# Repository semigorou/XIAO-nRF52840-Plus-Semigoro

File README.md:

# XIAO nRF52840 Plus - Semigorou

Rev Oでは、Plusの追加端子D11〜D19に対応するφ0.65 mm穴を左右9個ずつ設け、左右ともD0〜D19の接続点を用意しました。使用中の信号は既存回路へ接続し、未使用端子も取り出せます。D16は電池測定、D14/D15はNFC兼用です。接触・はんだ付け方法は未確定で、穴を設けただけではXIAOと自動接続しません。通常端子のパッド径は1.4 mm（穴径1.0 mm）、信号配線幅は基本0.15 mm・最小0.13 mm、信号間隔0.15 mmです。DRC違反0・未接続0を確認しました。

B面の左右に2行で印字しました。1行目は https://github.com/semigorou、2行目は XIAO nRF52840 Plus - Semigorou です。B面を正面から見て、左は上から下、右は下から上へ読める向きです。

> **Rev Oの取付構成は、左右ともXIAOをB面、電源スイッチ・RESETボタンをF面です。** 左XIAOの14端子と左スイッチ配置を反転して再配線し、出力Gerberの実装面と位置決め穴も検証しました。基板にはXIAO B・PWR F・RST FおよびF/Bを印字しています。

Y13 Rev O試作基板とXIAO用ZMK設定。Rev OでもGPIO信号の割当はRev Gから維持しています。左右各XIAO nRF52840 Plus、左エンコーダー、右PMW3610に対応する試作用ファームウェアです。ビルド成功と実機動作確認は別です。実機試験はこれからです。
またPCBについては、もともとnice!nano v2を搭載するPCBをベースに設計してます。nice!nano v2はBluetooth通信に対応していますが、日本の技適認証を取得していないため、日本国内での使用を想定し、技適認証に対応したXIAO nRF52840 Plusへ変更しました。

## Rev O 基板の発注データ

**[発注用Gerber ZIP](hardware/revO/Y13-XIAO-revO-order-gerbers.zip?raw=true)** · **[基板画像・発注／組立メモ](hardware/revO/README.md)**

2層・FR-4・板厚1.6 mm。XIAOの部品面をキャリアへ向けるRev Oです。旧Rev G以前のGerberは使用しないでください。取付高さと支持部材は実物で調整する前提の少量試作用で、ケース適合・電池充電・実機動作は未検証です。

左4×6＋5＝29キー、右4×6＋3＝27キー＋トラックボールに対応します。UF2名のrevGは既存ファームウェアの名前で、旧基板の取付方向を示すものではありません。

## 構成

- **右が親機（central）**。PCへのUSB／Bluetooth接続は右側を使います。左は子機。
- 左右各5行×6列。既存キーマップの配置・4レイヤー・56キーの割当を継承。60キー分のGPIOがあっても、空いている4位置は現キーマップに登録していません。
- 左エンコーダー：D6/P1.11、D8/P1.13、GND。
- 右PMW3610：SCLK D8/P1.13、SDIO D19/P1.07、NCS D13/P1.01、MOTION D6/P1.11。SPIのMOSI/MISOは同じSDIO線です。
- 左J7の予備D13/P1.01、D17/P1.03、D18/P1.05は予約のみ。キー等へ割り当てず、ファームウェアから駆動しません。
- 電池電圧はXIAO標準のP0.31とP0.14制御の分圧回路で取得。
- 充電電流選択P0.13は起動時に無プル入力とし、公称約50 mAを選びます。**D13/P1.01とは別ピン**です。100 mAモードは実装していません。
- RF送信出力を独自に上げる設定は移植していません。ソフトウェアだけで技適や組立後の無線適合を保証するものではありません。

ZMK v0.3の固定コミットと、元のDoctorWangWang PMW3610ドライバーの固定コミットを使用します。v0.3でのボード名は`seeeduino_xiao_ble`です。Plusの追加端子はGPIO番号で指定します。外付けQSPIフラッシュは使わず、設定はnRF内部フラッシュへ保存します。

## ダウンロードと書き込み

1. このリポジトリの **Actions → Build XIAO Plus Rev G firmware** を開き、成功した実行の`firmware`をダウンロード・展開します。
2. 初回またはペアリング不整合時は、左右ともRESETを素早く2回押してUSBドライブを表示し、`charybdis-xiao-plus-settings-reset.uf2`を各XIAOへコピーします。保存済みペアリング等が消えます。
3. 再度ブートローダーへ入り、左には`charybdis-xiao-plus-revG-left.uf2`、右には`charybdis-xiao-plus-revG-right-central.uf2`をコピーします。
4. 両側を起動し、右をUSBでPCへ接続してキーを確認します。その後、PCからBluetoothの`Charybdis XIAO+`へ接続します。

PCB上のRESETボタンを使うにはキャリアRESET端子からXIAO TP2への追加線が必要です。電源スイッチは電池＋だけを切ります。USB接続中の完全な電源OFFではありません。

## 電池と通電前確認

3.7 V・満充電4.2 Vの単セル電池を左右に1個ずつ独立接続する構成です。**電池の許容充電電流・保護回路は未確認**で、キャリアに逆接保護はありません。電池の極性、電源―GND短絡、追加線の導通を確認し、最初は電池を外してUSBで確認してください。

内蔵充電ICの約10時間タイマーに対し、50 mAでは400 mAhも充電状態によって時間切れの可能性があり、1100 mAhを深い放電から1回で満充電する用途には適合未確認です。このファームウェアはタイマー制限を解決しません。電池の仕様確認と実測が必要です。充電には電源SWをONにします。

USB位置の公差、ピン・スペーサーの固定と絶縁、スイッチの実物適合、電池固定、ケース収納は別途確認が必要です。元のnice!nano用UF2は書き込まないでください。

## 配線・変更

`docs/wiring.csv`がRev OのXIAO―キャリア対応、`docs/trackball.csv`が右の横一列6端子です。D11〜D19はXIAOの追加端子位置に対応した穴で接続する構造に変更しました。従来の離れた追加配線用穴は置換しています。接触方法・ピン長・支持部材は別途選定が必要です。BAT+とRESETの追加接続も残ります。主端子14本だけでは全機能は接続されません。

行はD1/D2/D4/D5/D7、列はD3/D0/D9/D10/D11/D12。ダイオード方向は元設定の`row2col`を維持。ボール方向・感度は既存設定を継承し、実物で必要なら調整します。予備GPIOの用途を追加する場合は対応する設定も変更してください。

## 出典

- 元設定・キーマップ：https://github.com/Semigoro23/zmk-config-nicenanov2-GERBER-adapter_Y13 （b3e0c08964bd929275c06698c74caaf6f8720078）
- ZMK：https://github.com/zmkfirmware/zmk （edf5c0814fd3ea202e43aad2d68fd32e882a518c）
- PMW3610：https://github.com/DoctorWangWang/zmk-pmw3610-driver （1d9c2c68ca76012e1b1e5f6ef02fa5eadc4ca399）
- Seeed公式：https://wiki.seeedstudio.com/XIAO_BLE/
- 充電IC：https://www.ti.com/lit/ds/symlink/bq25100.pdf

既存ファイルの著作権・ライセンス表記を維持しています。上流ソースのライセンスは各リポジトリを参照してください。

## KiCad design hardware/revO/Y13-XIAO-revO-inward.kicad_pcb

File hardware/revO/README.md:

# XIAO nRF52840 Plus - Semigorou / Rev O

**[発注用Gerber ZIP](Y13-XIAO-revO-order-gerbers.zip?raw=true)**

FR-4・2層・板厚 **1.6 mm**。

Rev Oでは左右それぞれD11〜D19に対応するφ0.65 mmの追加穴を9個配置。D0〜D19の全接続点を用意。D16は電池電圧測定、D14/D15はNFC兼用。追加穴の接触・はんだ付け方法は未確定で、穴を増設するだけでXIAOと自動接続するものではない。BAT+とRESETの追加接続も残る。通常14端子のパッド径は1.4 mm、穴径1.0 mm。旧追加配線用の離れた端子穴は、新しい対応位置の穴へ置き換え。ネジ穴とUSB基準位置は維持。

B面の左右に1行目 https://github.com/semigorou、2行目 XIAO nRF52840 Plus - Semigorouを印字。B面を正面から見て、左は上から下、右は下から上へ読める向き。

|部品|左|右|
|---|---|---|
|XIAO nRF52840 Plus|B面|B面|
|RESETボタン|F面|F面|
|スライド電源|F面|F面|

XIAOの部品面はキャリアへ向ける。基板にはXIAO B、PWR F、RST F、F/Bを印字した。左の14端子をB面取付けに合わせて反転し、再配線している。

## F面

## B面から見た向き

## 配線・検証

- [取付と検証記録](verification-report.md)
- [ピン接続表](pin-connections.csv)
- [センサー配線表](trackball.csv)
- [DRC](drc.txt)は違反0・未配線0。
- [Gerber検証記録](verification.json)で基板とドリル位置を照合済み。電源の位置決め穴は左右2個ずつφ0.90 mm。

右下端子はF面からUSBを上に見てGND / MOTION / SCLK / SDIO / CS / VCC。

GPIO信号の割当は既存XIAO用ファームウェアと同じ。左右各5行6列で左29キー、右27キー＋トラックボールに対応する。

高さと支持部材は実物で調整する。修正版での実装・ケース適合・充電・無線動作は未検証。Rev J以前の取付構成・接続座標は旧版。

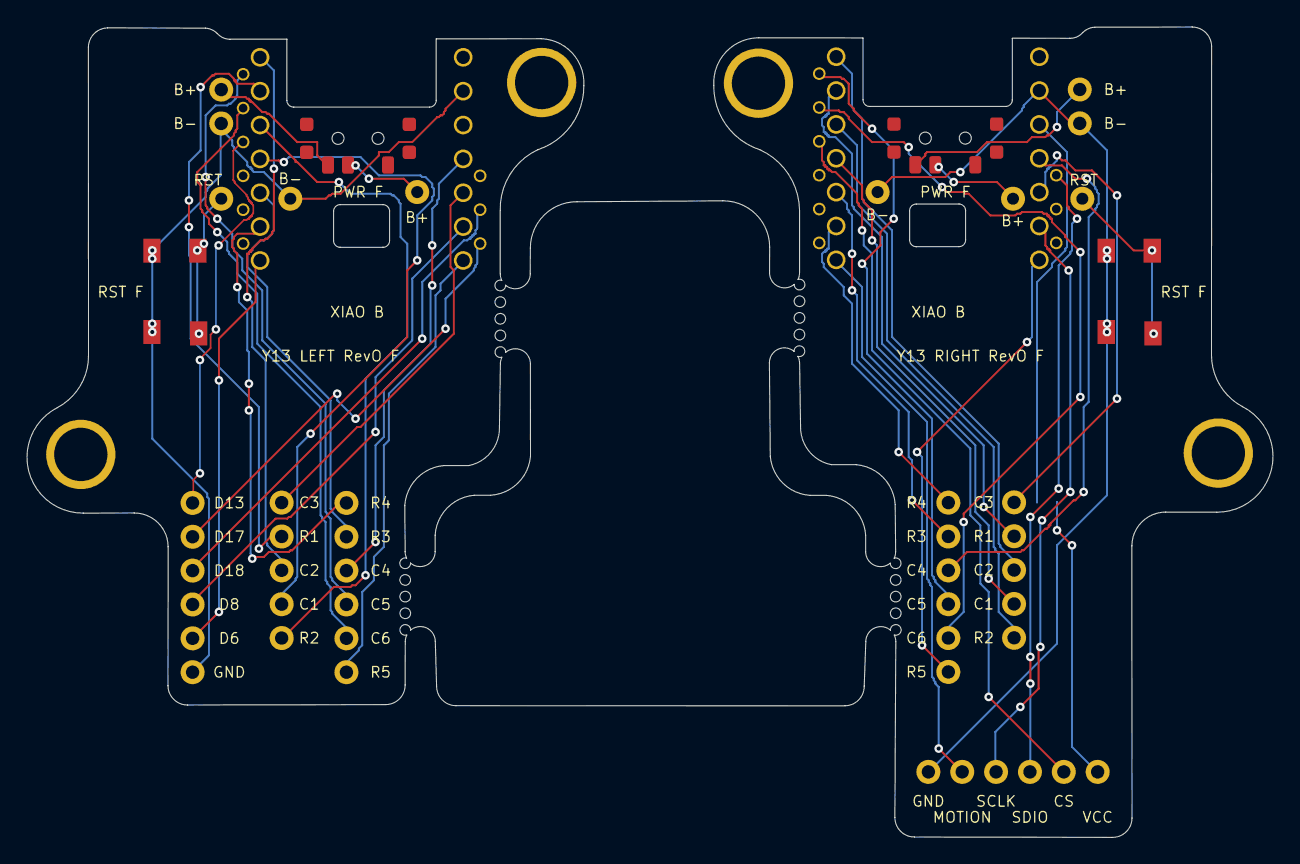
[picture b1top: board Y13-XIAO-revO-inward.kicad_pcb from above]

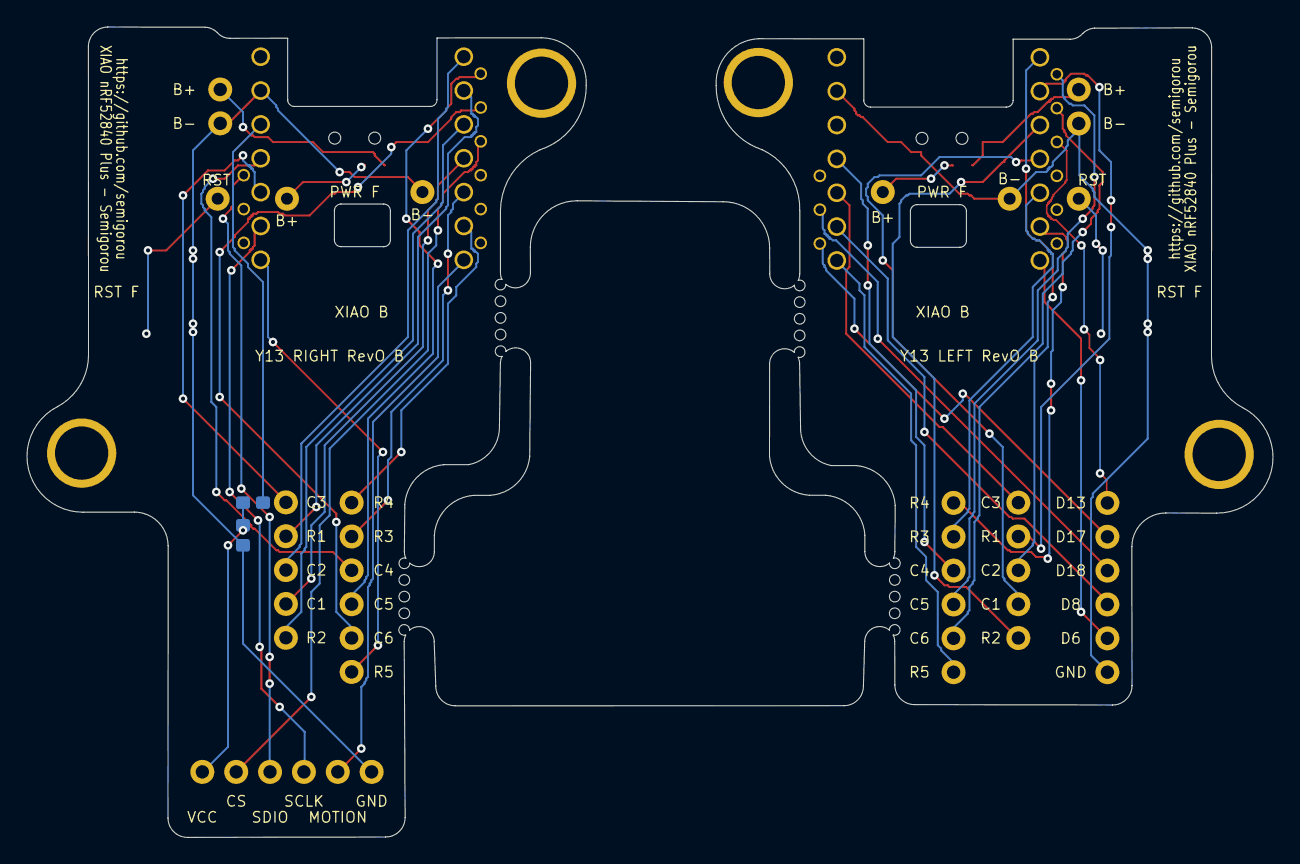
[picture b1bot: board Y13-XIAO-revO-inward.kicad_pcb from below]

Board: 2 copper layers, 93.5 x 60.8 mm, 28 parts (8 on the bottom side), 41 nets.

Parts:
C_SENSOR: 1uF 10V X7R 0603; C_SENSOR_DRAFT
J3: Original-position wire header; J3_DRAFT
J6: Original-position wire header; J6_DRAFT
J7: Original-position wire header; J7_DRAFT
J8: PMW3610 horizontal wire pads; J8_DRAFT
J9: Original-position wire header; J9_DRAFT
J10: Original-position wire header; J10_DRAFT
J11: Original-position wire header; J11_DRAFT
J12: Original-position wire header; J12_DRAFT
MB1, MB2, MB3, MB4, MB5, MB6, MB7, MB8, MB9, MB10, MB11, MB12: 0.8mm NPTH breakaway
R_SENSOR: 0R 0603; R_SENSOR_DRAFT
SW1, SW2: Original reset button
SW3: Reuse original slide switch; SW3_DRAFT
SW4: Reuse original slide switch; SW4_DRAFT
XIAO_L: XIAO Plus B SIDE; components toward carrier; XIAO_L_HEADER_DRAFT
XIAO_R: XIAO Plus B SIDE; components toward carrier; XIAO_R_HEADER_DRAFT

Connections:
3V3_R: R_SENSOR.1, XIAO_R.3V3
GND_L: J3.2, J7.6, SW1.2, XIAO_L.BAT-, XIAO_L.GND
GND_R: C_SENSOR.2, J6.2, J8.1, SW2.2, XIAO_R.BAT-, XIAO_R.GND
RESET_L: SW1.1, XIAO_L.RESET
RESET_R: SW2.1, XIAO_R.RESET
SENSOR_VDD_R: C_SENSOR.1, J8.6, R_SENSOR.2
SPARE_D13_L: J7.1, XIAO_L.D13
SPARE_D17_L: J7.2, XIAO_L.D17
SPARE_D18_L: J7.3, XIAO_L.D18
bat_l: SW3.2, XIAO_L.BAT+
bat_r: SW4.2, XIAO_R.BAT+
bat_sw_l: J3.1, SW3.3
bat_sw_r: J6.1, SW4.3
col1_l: J9.4, XIAO_L.D3
col1_r: J11.4, XIAO_R.D3
col2_l: J9.3, XIAO_L.D0
col2_r: J11.3, XIAO_R.D0
col3_l: J9.1, XIAO_L.D9
col3_r: J11.1, XIAO_R.D9
col4_l: J10.3, XIAO_L.D10
col4_r: J12.3, XIAO_R.D10
col5_l: J10.4, XIAO_L.D11
col5_r: J12.4, XIAO_R.D11
col6_l: J10.5, XIAO_L.D12
col6_r: J12.5, XIAO_R.D12
miso_l: J7.5, XIAO_L.D6
miso_r: J8.2, XIAO_R.D6
mosi_r: J8.4, XIAO_R.D19
rgb_l: J8.5, XIAO_R.D13
row1_l: J9.2, XIAO_L.D1
row1_r: J11.2, XIAO_R.D1
row2_l: J9.5, XIAO_L.D2
row2_r: J11.5, XIAO_R.D2
row3_l: J10.2, XIAO_L.D4
row3_r: J12.2, XIAO_R.D4
row4_l: J10.1, XIAO_L.D5
row4_r: J12.1, XIAO_R.D5
row5_l: J10.6, XIAO_L.D7
row5_r: J12.6, XIAO_R.D7
sc_l: J7.4, XIAO_L.D8
sc_r: J8.3, XIAO_R.D8
